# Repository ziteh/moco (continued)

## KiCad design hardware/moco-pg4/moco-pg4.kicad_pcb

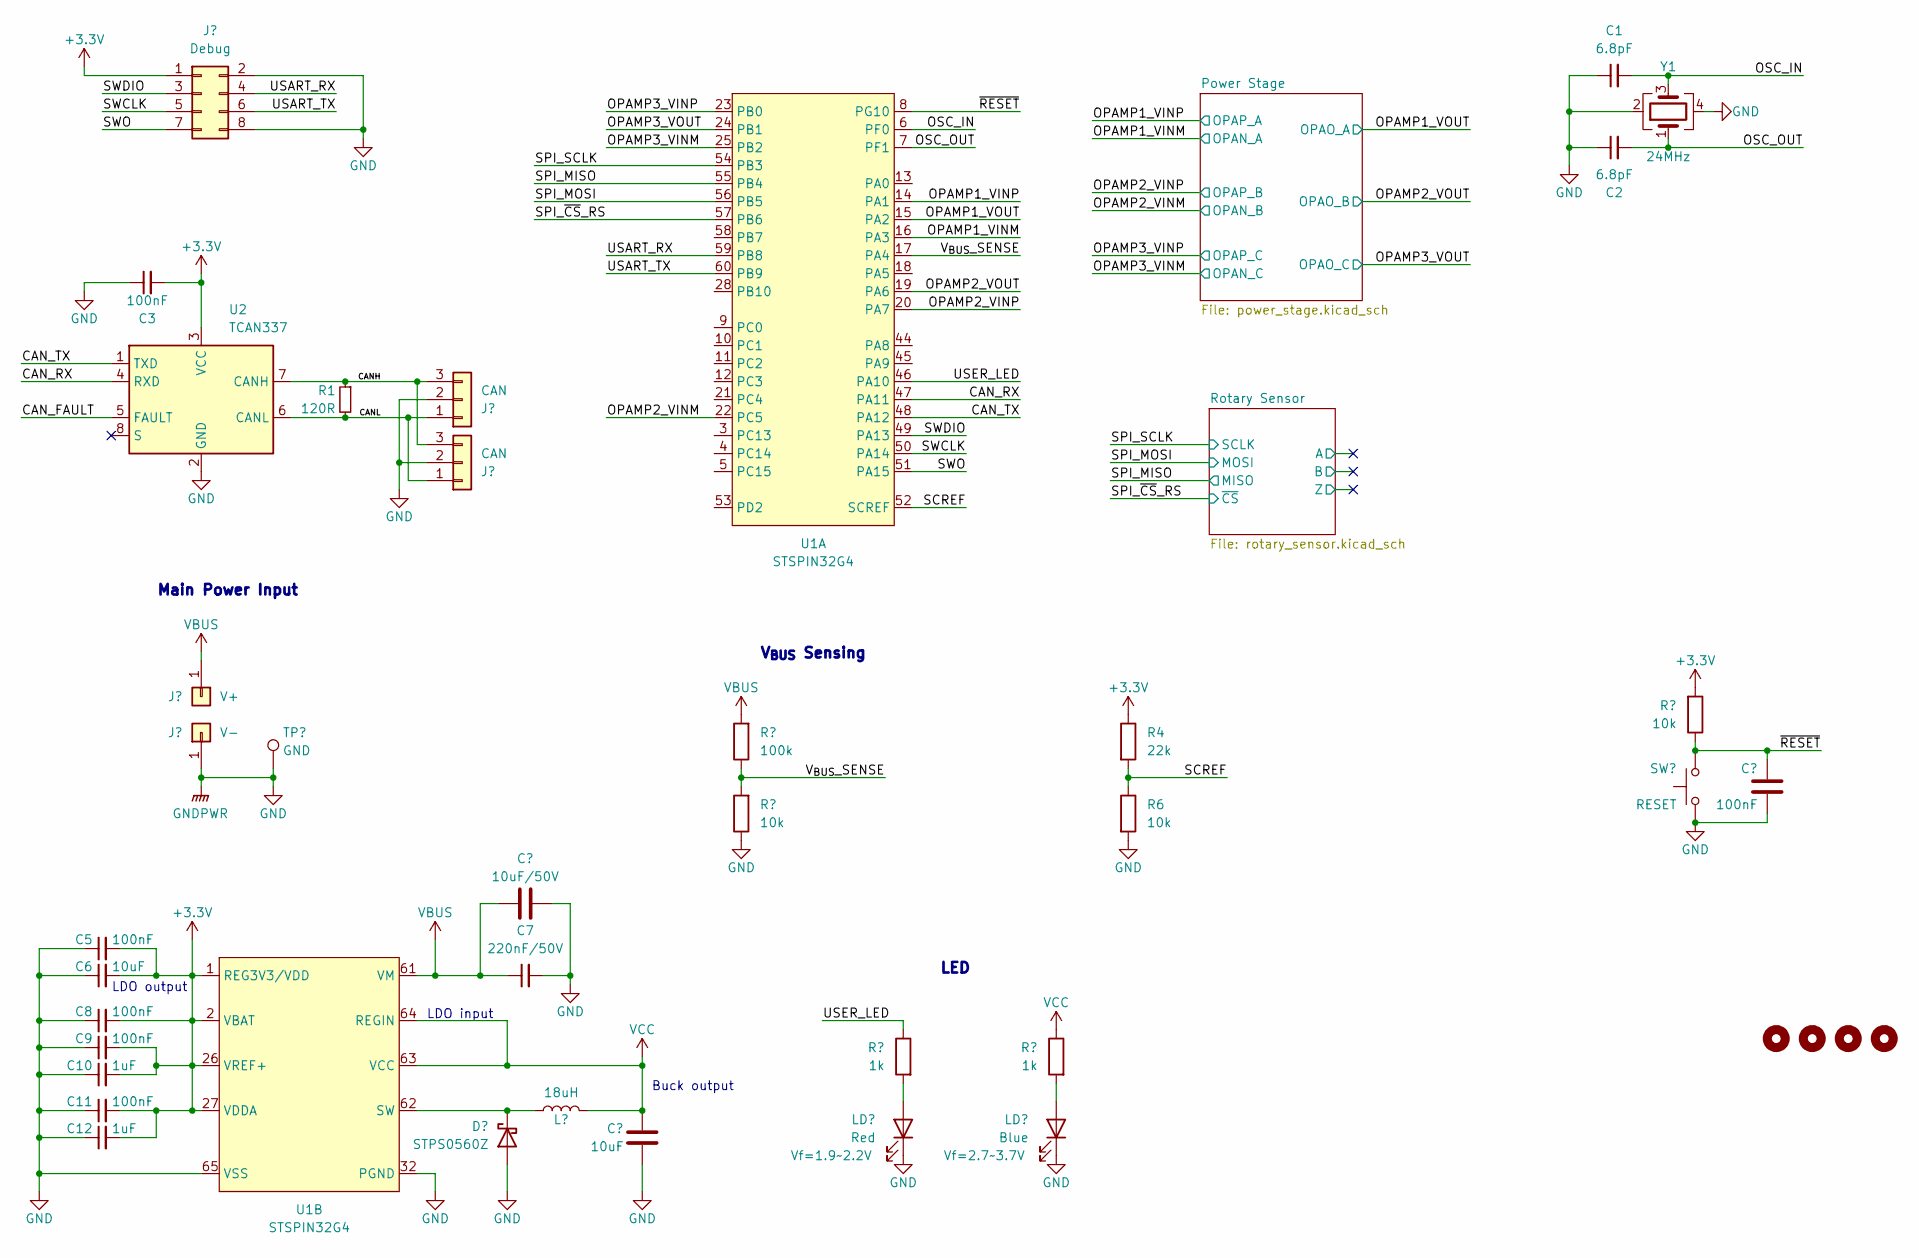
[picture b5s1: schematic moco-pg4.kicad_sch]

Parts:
C1, C2: 6.8pF; C_0402_1005Metric; MFR. Part# 0402CG6R8C500NT; LCSC C1576
C3, C4, C5, C8, C9, C11: 100nF; C_0402_1005Metric; MFR. Part# CL05B104KB54PNC; LCSC C307331
C6: 10uF; C_0402_1005Metric; MFR. Part# CL05A106MQ5NUNC; LCSC C15525
C7: 220nF/50V; C_0805_2012Metric; MFR. Part# CL21B224KBFNNNE; LCSC C5378
C10, C12: 1uF; C_0402_1005Metric; MFR. Part# CL05A105KA5NQNC; LCSC C52923
C13: 10uF; C_0805_2012Metric; MFR. Part# CL21A476MQYNNNE; LCSC C16780
C35: 10uF/50V; C_0805_2012Metric; MFR. Part# GRM21BR61H106KE43L; LCSC C440198
D1: STPS0560Z; D_SOD-123F; MFR. Part# STPS0560Z; LCSC C99285
H1, H2, H3, H4: MountingHole; MountingHole_2.2mm_M2_ISO14580
J1: Debug; PinHeader_2x04_P2.54mm_Vertical
J2, J8: CAN; JST_SH_SM03B-SRSS-TB_1x03-1MP_P1.00mm_Horizontal; MFR. Part# SM03B-SRSS-TB(LF)(SN); LCSC C160403
J3: V+; wire_2.2mm_rectagnel
J4: V-; wire_2.2mm
L1: 18uH; L_Taiyo-Yuden_MD-3030; MFR. Part# YNR3015-220M; LCSC C497564
LD1: Red; LED_0603_1608Metric; MFR. Part# KT-0603R; LCSC C2286
LD2: Blue; LED_0603_1608Metric; MFR. Part# 19-217/GHC-YR1S2/3T; LCSC C72043
R1: 120R; R_0402_1005Metric_Pad0.72x0.64mm_HandSolder; MFR. Part# 0402WGF1200TCE; LCSC C25079
R2, R5, R6: 10k; R_0402_1005Metric; MFR. Part# 0402WGF1002TCE; LCSC C25744
R3: 100k; R_0402_1005Metric; MFR. Part# 0402WGF1003TCE; LCSC C25741
R4: 22k; R_0402_1005Metric; MFR. Part# 0402WGF2202TCE; LCSC C25768
R7, R8: 1k; R_0402_1005Metric; MFR. Part# 0402WGF1001TCE; LCSC C11702
SW1: RESET; SW_SPST_EVQP7C; MFR. Part# 3*4mm
TP1: GND; TestPoint_Pad_D1.0mm
U1: STSPIN32G4; VFQFPN 9X9X1.0 64 PITCH 0.5; MFR. Part# STSPIN32G4; LCSC C2858620
U2: TCAN337; SOT-23-8
Y1: 24MHz; Crystal_SMD_3225-4Pin_3.2x2.5mm; MFR. Part# X322524MSB4SI; LCSC C15643

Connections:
+3.3V: C3.2, C5.2, C6.2, C8.2, C9.2, C10.2, C11.2, C12.2, J1.1, R2.2, R4.1, U1.1 (REG3V3/VDD), U1.2 (VBAT), U1.26 (VREF+), U1.27 (VDDA), U2.3 (VCC); also elsewhere on the board
/CANH: J2.3, J8.3, R1.1, U2.7 (CANH)
/CANL: J2.1, J8.1, R1.2, U2.6 (CANL)
/CAN_FAULT: U2.5 (FAULT)
/CAN_RX: U1.47 (PA11), U2.4 (RXD)
/CAN_TX: U1.48 (PA12), U2.1 (TXD)
/OPAMP1_VINM: U1.16 (PA3); also elsewhere on the board
/OPAMP1_VINP: U1.14 (PA1); also elsewhere on the board
/OPAMP1_VOUT: U1.15 (PA2); also elsewhere on the board
/OPAMP2_VINM: U1.22 (PC5); also elsewhere on the board
/OPAMP2_VINP: U1.20 (PA7); also elsewhere on the board
/OPAMP2_VOUT: U1.19 (PA6); also elsewhere on the board
/OPAMP3_VINM: U1.25 (PB2); also elsewhere on the board
/OPAMP3_VINP: U1.23 (PB0); also elsewhere on the board
/OPAMP3_VOUT: U1.24 (PB1); also elsewhere on the board
/OSC_IN: C1.2, U1.6 (PF0), Y1.3
/OSC_OUT: C2.2, U1.7 (PF1), Y1.1
/SCREF: R4.2, R6.1, U1.52 (SCREF)
/SPI_MISO: U1.55 (PB4); also elsewhere on the board
/SPI_MOSI: U1.56 (PB5); also elsewhere on the board
/SPI_SCLK: U1.54 (PB3); also elsewhere on the board
/SPI_~CS_RS: U1.57 (PB6); also elsewhere on the board
/SWCLK: J1.5, U1.50 (PA14)
/SWDIO: J1.3, U1.49 (PA13)
/SWO: J1.7, U1.51 (PA15)
/USART_RX: J1.4, U1.59 (PB8)
/USART_TX: J1.6, U1.60 (PB9)
/USER_LED: R7.1, U1.46 (PA10)
/V_{BUS}_SENSE: R3.1, R5.2, U1.17 (PA4)
/~RESET: C4.1, R2.1, SW1.1, U1.8 (PG10)
GND: C1.1, C2.1, C3.1, C4.2, C5.1, C6.1, C7.2, C8.1, C9.1, C10.1, C11.1, C12.1, C13.2, D1.2 (A), J1.2, J1.8, J2.2, J4.1, J8.2, LD1.1 (K), LD2.1 (K), R5.1, R6.2, SW1.2, TP1.1, U1.32 (PGND), U1.65 (VSS), U2.2 (GND), Y1.2, Y1.4; also elsewhere on the board
unnamed: D1.1 (K), L1.1, U1.62 (SW)
unnamed: LD1.2 (A), R7.2
unnamed: LD2.2 (A), R8.2
VBUS: C7.1, J3.1, R3.2, U1.61 (VM); also elsewhere on the board
VCC: C13.1, L1.2, R8.1, U1.63 (VCC), U1.64 (REGIN)

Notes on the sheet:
Buck output
LDO output
LED
Main Power Input
V_{BUS} Sensing
LDO input

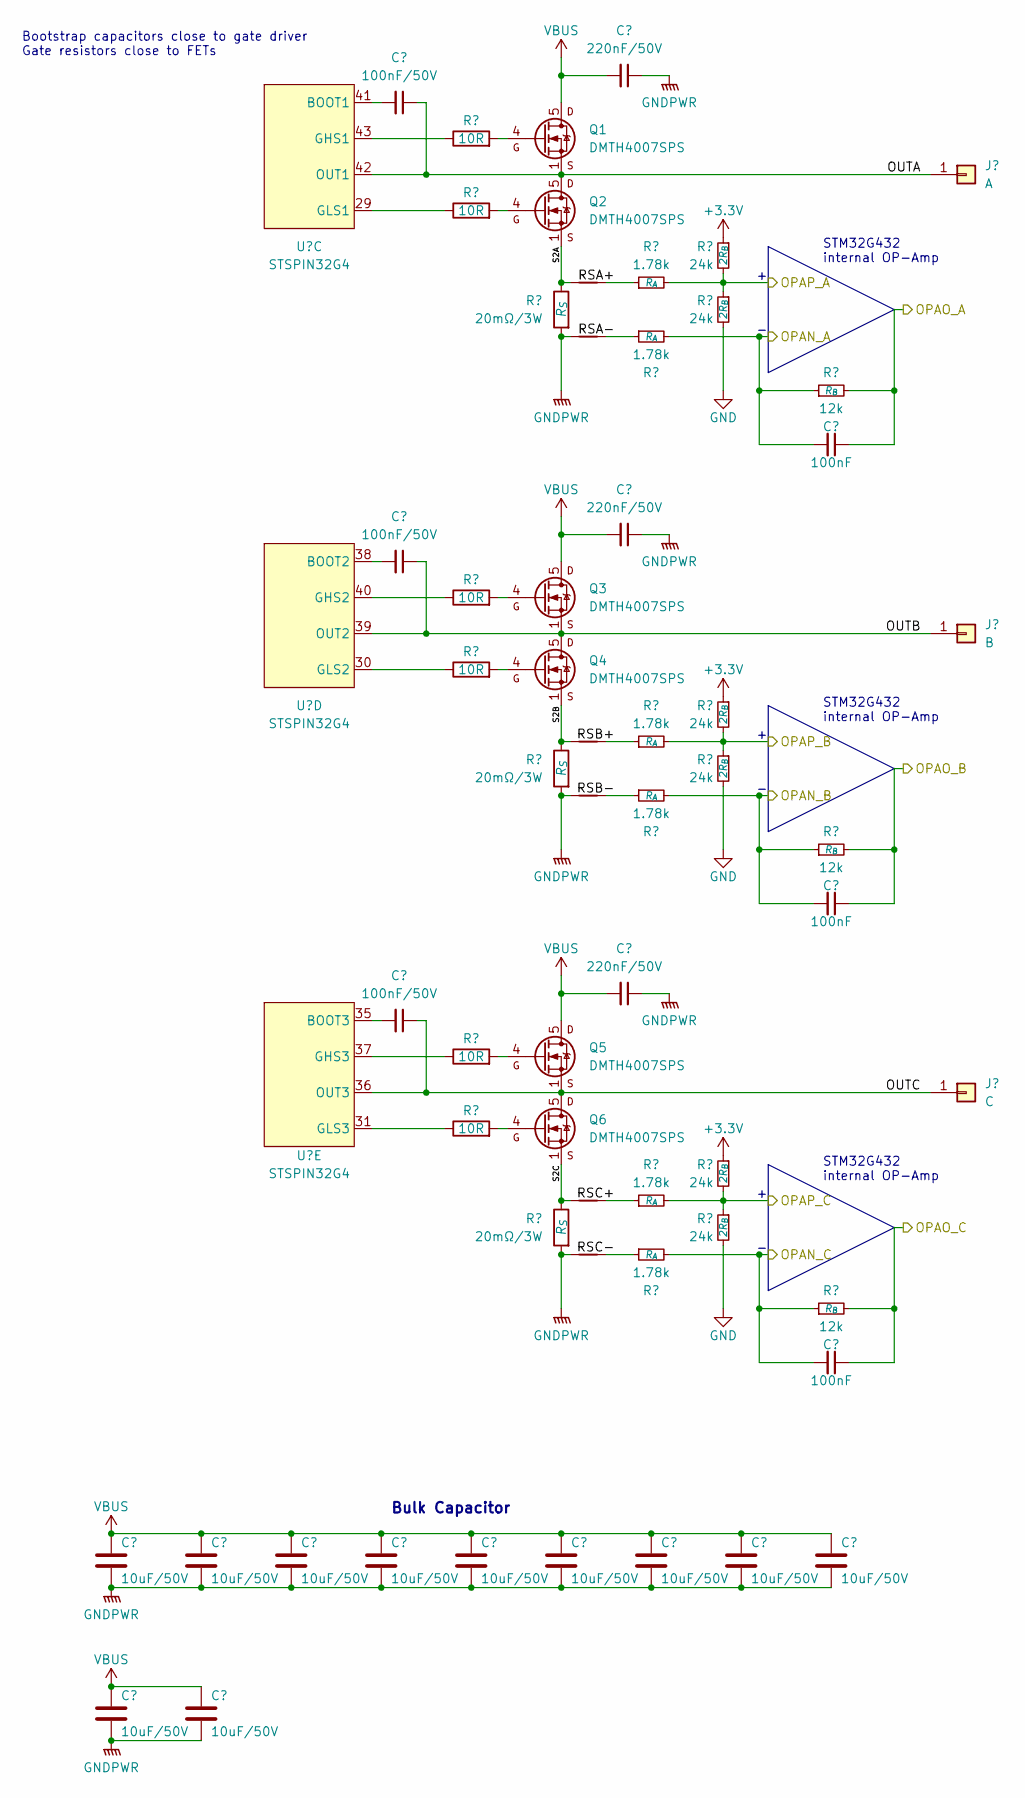
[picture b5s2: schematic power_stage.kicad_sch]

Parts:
C14, C17, C20: 220nF/50V; C_0805_2012Metric; MFR. Part# CL21B224KBFNNNE; LCSC C5378
C15, C18, C21: 100nF/50V; C_0402_1005Metric; MFR. Part# CL05B104KB54PNC; LCSC C307331
C16, C19, C22: 100nF; C_0402_1005Metric; MFR. Part# CL21B224KBFNNNE; LCSC C5378
C23, C24, C25, C26, C27, C28, C29, C30, C31, C33, C34: 10uF/50V; C_0805_2012Metric; MFR. Part# GRM21BR61H106KE43L; LCSC C440198
J5: A; wire_2.2mm_rectagnel
J6: B; wire_2.2mm_rectagnel
J7: C; wire_2.2mm_rectagnel
NT1, NT2, NT3, NT4, NT5, NT6: NetTie_2; NetTie-2_SMD_Pad0.5mm
Q1, Q2, Q3, Q4, Q5, Q6: DMTH4007SPS; PowerDI5060-8
R9, R10, R17, R18, R25, R26: 10R; R_0402_1005Metric; MFR. Part# 0402WGF100JTCE; LCSC C25077
R11, R14, R19, R22, R27, R30: 24k; R_0402_1005Metric; MFR. Part# 0402WGF2402TCE; LCSC C25769
R12, R15, R20, R23, R28, R31: 1.78k; R_0402_1005Metric; MFR. Part# ARG02FTC1781; LCSC C284379
R13, R21, R29: 20mΩ/3W; R_2512_6332Metric; MFR. Part# CRA2512-FZ-R020ELF; LCSC C840620
R16, R24, R32: 12k; R_0402_1005Metric; MFR. Part# 0402WGF1202TCE; LCSC C25752
U1: STSPIN32G4; VFQFPN 9X9X1.0 64 PITCH 0.5; MFR. Part# STSPIN32G4; LCSC C2858620

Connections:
+3.3V: R11.1, R19.1, R27.1; also elsewhere on the board
/OPAMP1_VINM: C16.2, R15.2, R16.1; also elsewhere on the board
/OPAMP1_VINP: R11.2, R12.2, R14.1; also elsewhere on the board
/OPAMP1_VOUT: C16.1, R16.2; also elsewhere on the board
/OPAMP2_VINM: C19.2, R23.2, R24.1; also elsewhere on the board
/OPAMP2_VINP: R19.2, R20.2, R22.1; also elsewhere on the board
/OPAMP2_VOUT: C19.1, R24.2; also elsewhere on the board
/OPAMP3_VINM: C22.2, R31.2, R32.1; also elsewhere on the board
/OPAMP3_VINP: R27.2, R28.2, R30.1; also elsewhere on the board
/OPAMP3_VOUT: C22.1, R32.2; also elsewhere on the board
/Power Stage/OUTA: C15.1, J5.1, Q1.1 (S), Q1.2 (S), Q1.3 (S), Q2.5 (D), Q2.6 (D), Q2.7 (D), Q2.8 (D), U1.42 (OUT1)
/Power Stage/OUTB: C18.1, J6.1, Q3.1 (S), Q3.2 (S), Q3.3 (S), Q4.5 (D), Q4.6 (D), Q4.7 (D), Q4.8 (D), U1.39 (OUT2)
/Power Stage/OUTC: C21.1, J7.1, Q5.1 (S), Q5.2 (S), Q5.3 (S), Q6.5 (D), Q6.6 (D), Q6.7 (D), Q6.8 (D), U1.36 (OUT3)
/Power Stage/RSA+: NT1.1, R12.1
/Power Stage/RSA-: NT2.1, R15.1
/Power Stage/RSB+: NT3.1, R20.1
/Power Stage/RSB-: NT4.1, R23.1
/Power Stage/RSC+: NT5.1, R28.1
/Power Stage/RSC-: NT6.1, R31.1
/Power Stage/S2A: NT1.2, Q2.1 (S), Q2.2 (S), Q2.3 (S), R13.1
/Power Stage/S2B: NT3.2, Q4.1 (S), Q4.2 (S), Q4.3 (S), R21.1
/Power Stage/S2C: NT5.2, Q6.1 (S), Q6.2 (S), Q6.3 (S), R29.1
GND: C14.1, C17.1, C20.1, C23.2, C24.2, C25.2, C26.2, C27.2, C28.2, C29.2, C30.2, C31.2, C33.2, C34.2, NT2.2, NT4.2, NT6.2, R13.2, R14.2, R21.2, R22.2, R29.2, R30.2; also elsewhere on the board
unnamed: Q1.4 (G), R9.2
unnamed: Q2.4 (G), R10.2
unnamed: Q3.4 (G), R17.2
unnamed: Q4.4 (G), R18.2
unnamed: Q5.4 (G), R25.2
unnamed: Q6.4 (G), R26.2
unnamed: C15.2, U1.41 (BOOT1)
unnamed: R9.1, U1.43 (GHS1)
unnamed: R10.1, U1.29 (GLS1)
unnamed: C18.2, U1.38 (BOOT2)
unnamed: R17.1, U1.40 (GHS2)
unnamed: R18.1, U1.30 (GLS2)
unnamed: C21.2, U1.35 (BOOT3)
unnamed: R25.1, U1.37 (GHS3)
unnamed: R26.1, U1.31 (GLS3)
VBUS: C14.2, C17.2, C20.2, C23.1, C24.1, C25.1, C26.1, C27.1, C28.1, C29.1, C30.1, C31.1, C33.1, C34.1, Q1.5 (D), Q1.6 (D), Q1.7 (D), Q1.8 (D), Q3.5 (D), Q3.6 (D), Q3.7 (D), Q3.8 (D), Q5.5 (D), Q5.6 (D), Q5.7 (D), Q5.8 (D); also elsewhere on the board

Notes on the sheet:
Bulk Capacitor
STM32G432 internal OP-Amp
Bootstrap capacitors close to gate driver Gate resistors close to FETs

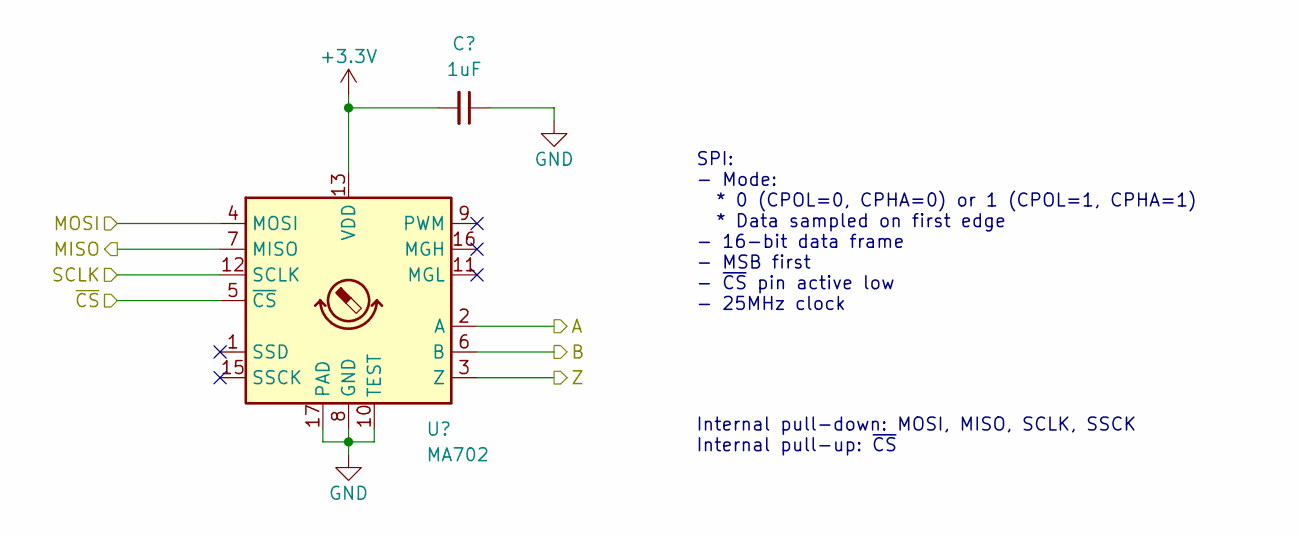
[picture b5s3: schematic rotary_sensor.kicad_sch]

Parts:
C36: 1uF; C_0402_1005Metric_Pad0.74x0.62mm_HandSolder; MFR. Part# CL05A105KA5NQNC; LCSC C52923
U3: MA702; QFN-16-1EP_3x3mm_P0.5mm_EP1.75x1.75mm; MFR. Part# MA702GQ-Z

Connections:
+3.3V: C36.2, U3.13 (VDD); also elsewhere on the board
/Rotary Sensor/A: U3.2 (A)
/Rotary Sensor/B: U3.6 (B)
/Rotary Sensor/Z: U3.3 (Z)
/SPI_MISO: U3.7 (MISO); also elsewhere on the board
/SPI_MOSI: U3.4 (MOSI); also elsewhere on the board
/SPI_SCLK: U3.12 (SCLK); also elsewhere on the board
/SPI_~CS_RS: U3.5 (~CS); also elsewhere on the board
GND: C36.1, U3.8 (GND), U3.10 (TEST), U3.17 (PAD); also elsewhere on the board

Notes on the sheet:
Internal pull-down: MOSI, MISO, SCLK, SSCK Internal pull-up: ~{CS}
SPI: - Mode: * 0 (CPOL=0, CPHA=0) or 1 (CPOL=1, CPHA=1) * Data sampled on first edge - 16-bit data frame - MSB first - ~{CS} pin active low - 25MHz clock

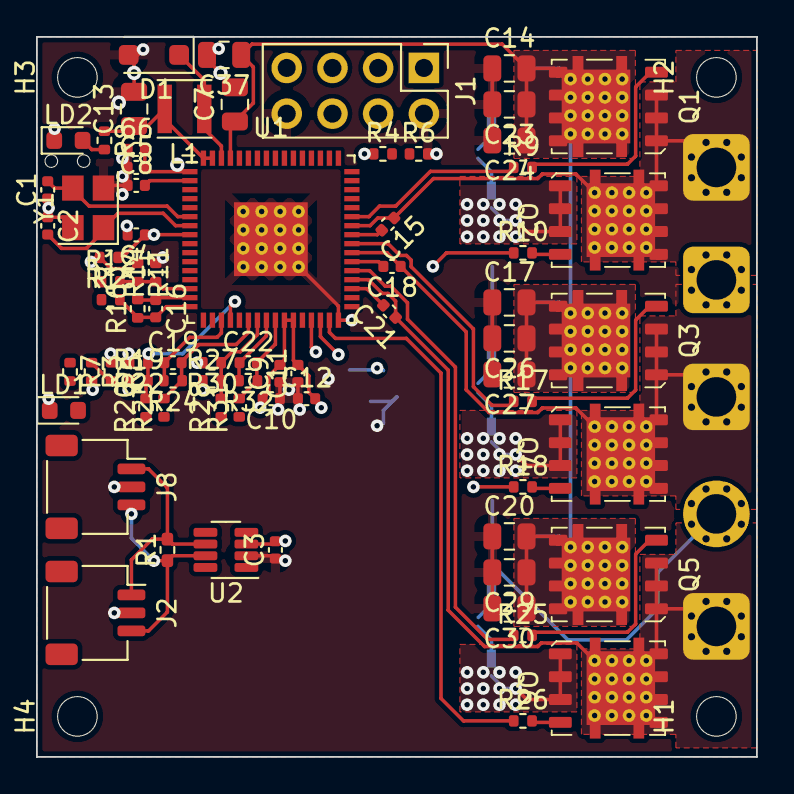
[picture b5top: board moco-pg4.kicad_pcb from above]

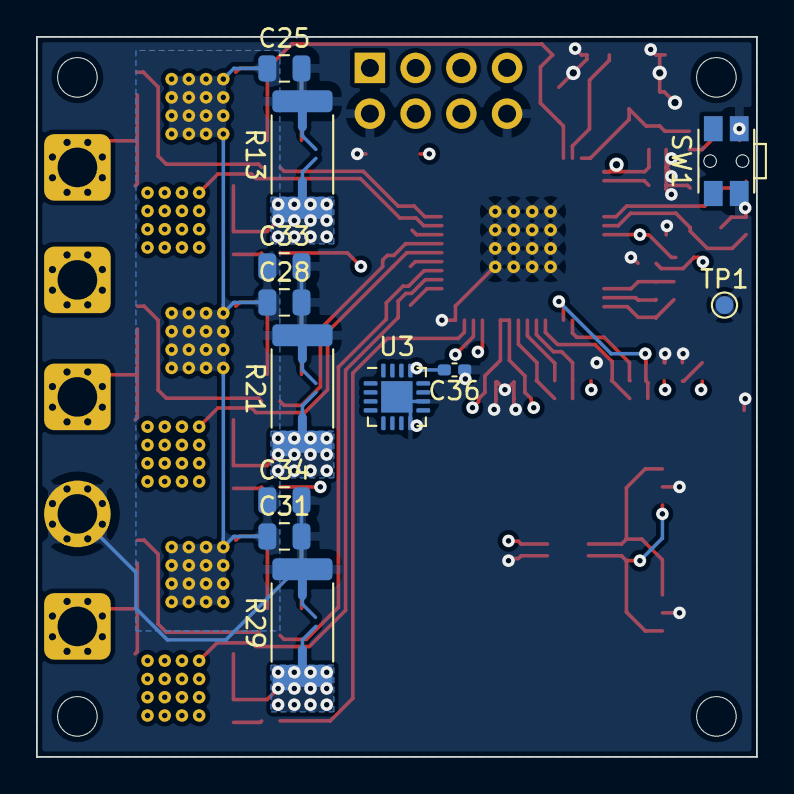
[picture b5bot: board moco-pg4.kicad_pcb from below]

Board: 4 copper layers, 40.0 x 40.0 mm, 101 parts (18 on the bottom side), 62 nets.

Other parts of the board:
C37: 10uF/50V; C_0805_2012Metric

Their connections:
GND: C37.2; also elsewhere on the board
VBUS: C37.1; also elsewhere on the board

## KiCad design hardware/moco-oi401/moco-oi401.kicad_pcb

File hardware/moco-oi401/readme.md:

# moco-OI401

- 10V~35V operating voltage
- 8A peak current
- 3x or 6xPWM control
- 3-Phase low-side current sense
- Ø40mm round PCB
- 3xM2 mounting holes, P.C.D Ø35.5mm
- [STM32G431CBU6](https://www.st.com/en/microcontrollers-microprocessors/stm32g431cb.html) 170 MHz MCU
- [DRV8316C](https://www.ti.com/product/DRV8316C) gate driver integrated FETs
- AS5047x magnetic encoder

## Pinmap

| Description              | DRV8316 | STM32 | STM32 Func |
| ------------------------ | ------- | ----- | ---------- |
| PWM-A High               | INHA    | PA10  | TIM1_CH3   |
| PWM-B High               | INHB    | PA9   | TIM1_CH2   |
| PWM-C High               | INHC    | PA8   | TIM1_CH1   |
| PWM-A Low                | INLA    | PC15  | TIM1_CH3N  |
| PWM-B Low                | INLB    | PA12  | TIM1_CH2N  |
| PWM-C Low                | INLC    | PB13  | TIM1_CH1N  |
| Current sense A          | SOA     | PA5   | ADC2_IN13  |
| Current sense B          | SOB     | PA6   | ADC2_IN3   |
| Current sense C          | SOC     | PA7   | ADC2_IN4   |
| nEnable                  | DRVOFF  | PB12  |            |
| nFAULT                   | nFAULT  | PB11  |            |
| SPI SCLK                 | SCLK    | PB3   | SPI1       |
| SPI MISO                 | SDI     | PB4   | SPI1       |
| SPI MOSI                 | SDO     | PB5   | SPI1       |
| SPI nCS DRV8316          | nSCS    | PB9   |            |
| SPI nCS AS5047x          | --      | PB2   |            |
| USART Tx                 | --      | PA2   | USART2     |
| USART Rx                 | --      | PA3   | USART2     |
| User LED 1 (Red)         | --      | PA0   | Active LOW |
| User LED 2 (Blue)        | --      | PA1   | Active LOW |
| 5V indicator LED (Green) | --      | --    |            |

## Jumper
- SB1 (3.3V LDO Bypass)
  - ON: 3.3V LDO bypassed, 3.3V provided through the buck regulator of DRV8316.
  - OFF (Default): 3.3V provided through the LDO.
- SB2 (nSLEEP Reset)
  - ON: Connected DRV8316 `nSLEEP` pin to RESET button.
  - OFF (Default): Disconnected DRV8316 `nSLEEP` pin to RESET button.
- SB3 (Voltage Reference Selection)
  - ON (Default): Connected +3.3V to STM32 `VREF+` and DRV8316 `VREF/LILM`, `VREF+` used as input.
  - OFF: Disconnected +3.3V to STM32 `VREF+` and DRV8316 `VREF/LILM`, voltage reference powered by STM32G4 embed voltage reference buffer, `VREF+` used as output.

## SPI

- Mode=1
  - CPOL=0. Clock is low when idle.
  - CPHA=1. Data sampled on 2nd edge (i.e. falling edge).
- 16-bit data frame.
- MSB first.
- nCS pin active low.
- 5MHz clock (limited by DRV8316).

## Board Characteristics

- Copper layer count: 2
- Board overall dimensions: 40 x 40 mm
- Min track/spacing: 0.13 mm / 0.13 mm
- Min hole diameter: 0.3 mm
- Castellated pads: No
- Edge card connectors: No
- Plated board edge: No

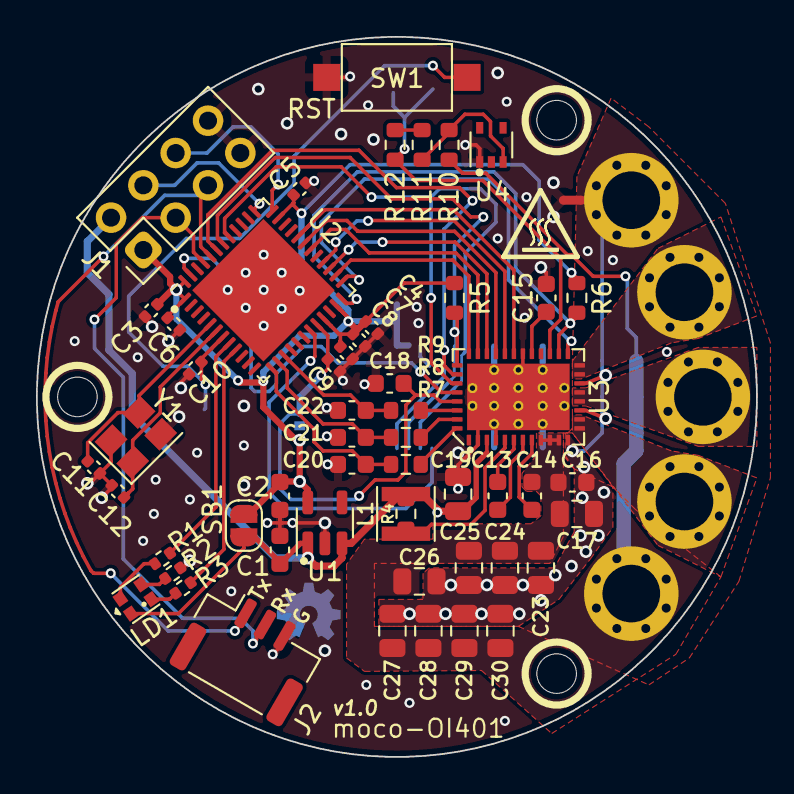
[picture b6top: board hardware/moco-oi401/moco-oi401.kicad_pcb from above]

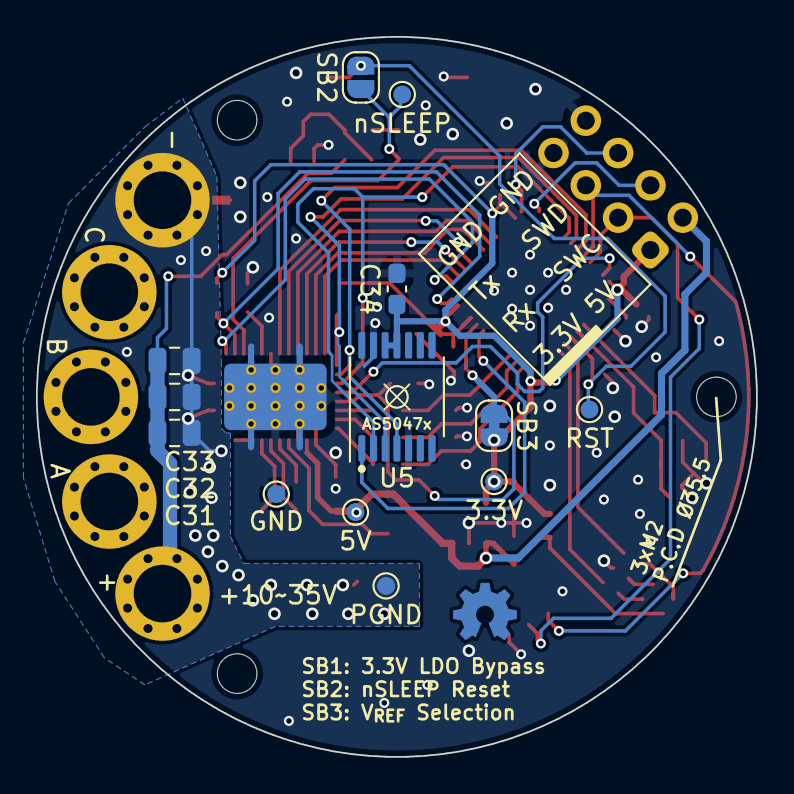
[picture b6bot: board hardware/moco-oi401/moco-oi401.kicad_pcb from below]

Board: 2 copper layers, 40.0 x 40.0 mm, 75 parts (13 on the bottom side), 48 nets.

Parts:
C1, C2: 1uF; C_0603_1608Metric
C3, C4, C5, C6, C9, C10: 100nF; C_0402_1005Metric
C7: 10nF; C_0402_1005Metric
C8: 1uF; C_0402_1005Metric
C11, C12: 12pF; C_0402_1005Metric
C13: 47nF/50V; C_0603_1608Metric
C14: 1uF/16V; C_0603_1608Metric
C15: 1uF/6.3V; C_0603_1608Metric
C16: 100nF/50V; C_0603_1608Metric
C17, C23, C24, C25, C26, C27, C28, C29, C30, C31, C32, C33: 10uF/50V; C_0805_2012Metric
C18: 100nF/6.3V; C_0603_1608Metric
C19: 22uF/16V; C_0805_2012Metric
C20, C21, C22: 22pF; C_0603_1608Metric
C34: 100nF; C_0603_1608Metric_Pad1.08x0.95mm_HandSolder
H1, H2, H3: MountingHole; MountingHole_2.2mm_M2_ISO14580
J1: Debug; PinHeader_2x04_P2.54mm_Vertical
J2: Serial; JST_GH_SM03B-GHS-TB_1x03-1MP_P1.25mm_Horizontal
J3: V+; wire_3.2mm
J4: V-; wire_3.2mm
J5: A; wire_3.2mm
J6: B; wire_3.2mm
J7: C; wire_3.2mm
L1: 47uH; L_Taiyo-Yuden_MD-3030
LD1: LED_BAGR; RGB LED 1.6x1.6mm
NT1: NetTie_2; NetTie-2_SMD_Pad0.5mm
R1, R3: 1k; R_0402_1005Metric
R2: 5.1k; R_0402_1005Metric
R4: 22R; R_0603_1608Metric
R5, R6: 5.1k; R_0603_1608Metric
R7, R8, R9: 330R; R_0603_1608Metric
R10: 10k/100mW; R_0603_1608Metric
R11, R12: 10k; R_0603_1608Metric
SB1, SB2: SolderJumper_2_Open; SolderJumper-2_P1.3mm_Open_RoundedPad1.0x1.5mm
SB3: SolderJumper_2_Bridged; SolderJumper-2_P1.3mm_Bridged_RoundedPad1.0x1.5mm
SW1: RESET; SW_SPST_CK_RS282G05A3
TP1: ~{RESET}; TestPoint_Pad_D1.0mm
TP2: V_{CC}; TestPoint_Pad_D1.0mm
TP3: GND; TestPoint_Pad_D1.0mm
TP4: V_{BK}; TestPoint_Pad_D1.0mm
TP5: PGND; TestPoint_Pad_D1.0mm
TP6: nSLEEP; TestPoint_Pad_D1.0mm
U1: RT9013-33GB; SOT-23-5
U2: STM32G431CBUx; QFN-48-1EP_7x7mm_P0.5mm_EP5.6x5.6mm
U3: DRV8316CR; VQFN-40_RGF_5x7mm_0.5mm_pitch_thermalpad
U4: LM4040A50; SOT-353_SC-70-5
U5: AS5047x; TSSOP-14_4.4x5mm_P0.65mm
Y1: 16MHz; Crystal_SMD_3225-4Pin_3.2x2.5mm

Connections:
+3.3V: C2.1, C3.1, C4.1, C5.1, C6.1, C7.1, C8.1, C34.2, J1.1, R5.1, R6.1, SB1.2 (B), SB3.2 (B), TP2.1, U1.5 (VOUT), U2.1 (VBAT), U2.21 (VDDA), U2.23 (VDD), U2.35 (VDD), U2.48 (VDD), U5.11 (VDD), U5.12 (VDD3V3)
+5V: C1.1, C19.2, J1.2, L1.2, LD1.2 (A), R4.2, SB1.1 (A), TP4.1, U1.1 (VIN), U1.3 (EN), U3.3 (FB_BK)
/ Rotary Sensor/MISO: R5.2, U2.42 (PB4), U3.33 (SDO), U5.3 (MISO)
/ Rotary Sensor/MOSI: U2.43 (PB5), U3.34 (SDI), U5.4 (MOSI)
/ Rotary Sensor/SCLK: U2.41 (PB3), U3.35 (SCLK), U5.2 (CLK)
/ Rotary Sensor/~CS: U2.19 (PB2), U5.1 (~CS)
/Driver/AVDD: C15.2, U3.25 (AVDD)
/Driver/DRVOFF: U2.25 (PB12), U3.21 (DRVOFF)
/Driver/INHA: U2.32 (PA10), U3.27 (INHA)
/Driver/INHB: U2.31 (PA9), U3.29 (INHB)
/Driver/INHC: U2.30 (PA8), U3.31 (INHC)
/Driver/INLA: U2.28 (PB15), U3.28 (INLA)
/Driver/INLB: U2.27 (PB14), U3.30 (INLB)
/Driver/INLC: U2.26 (PB13), U3.32 (INLC)
/Driver/OUTA: J5.1, U3.13 (OUTA), U3.14 (OUTA)
/Driver/OUTB: J6.1, U3.16 (OUTB), U3.17 (OUTB)
/Driver/OUTC: J7.1, U3.19 (OUTC), U3.20 (OUTC)
/Driver/SOA: C20.1, R7.1, U2.13 (PA5)
/Driver/SOB: C21.1, R8.1, U2.14 (PA6)
/Driver/SOC: C22.1, R9.1, U2.15 (PA7)
/Driver/V_{REF}: C9.1, C18.1, SB3.1 (A), U2.20 (VREF+), U3.37 (VREF/LILM)
/Driver/~CS: U2.47 (PB9), U3.36 (nSCS)
/Driver/~FAULT: R6.2, U2.24 (PB11), U3.22 (nFAULT)
/Driver/~SLEEP: R12.2, SB2.1 (A), TP6.1, U3.23 (nSLEEP)
/MCU/OSC_IN: C11.2, U2.5 (PF0), Y1.3
/MCU/OSC_OUT: C12.2, U2.6 (PF1), Y1.1
/SWCLK: J1.4, U2.37 (PA14)
/SWDIO: J1.6, U2.36 (PA13)
/UART1_RX: J1.3, J2.2, U2.45 (PB7)
/UART1_TX: J1.5, J2.1, U2.44 (PB6)
/USER_LED1: R1.2, U2.8 (PA0)
/USER_LED2: R3.2, U2.9 (PA1)
/~RESET: C10.1, SB2.2 (B), SW1.2, TP1.1, U2.7 (PG10)
GND: C1.2, C2.2, C3.2, C4.2, C5.2, C6.2, C7.2, C8.2, C9.2, C10.2, C11.1, C12.1, C15.1, C18.2, C19.1, C20.2, C21.2, C22.2, C34.1, J1.7, J1.8, J2.3, NT1.2, R2.2, SW1.1, TP3.1, U1.2 (GND), U2.49 (VSS), U3.2 (AGND), U3.4 (GND_BK), U3.26 (AGND), U3.41 (EP), U4.1 (A), U5.5 (TST), U5.13 (GND), Y1.2, Y1.4
GNDPWR: C16.1, C17.1, C23.2, C24.2, C25.2, C26.2, C27.2, C28.2, C29.2, C30.2, C31.2, C32.2, C33.2, J4.1, NT1.1, TP5.1, U3.12 (PGND), U3.15 (PGND), U3.18 (PGND)
unnamed: LD1.1 (BK), R3.1
unnamed: LD1.3 (GK), R2.1
unnamed: LD1.4 (RK), R1.1
unnamed: R11.2, R12.1
unnamed: C14.1, U3.8 (CP)
unnamed: C13.2, U3.7 (CPH)
unnamed: C13.1, U3.6 (CPL)
unnamed: R7.2, U3.40 (SOA)
unnamed: R8.2, U3.39 (SOB)
unnamed: R9.2, U3.38 (SOC)
unnamed: L1.1, R4.1, U3.5 (SW_BK)
unnamed: R10.2, R11.1, U4.3 (K)
Vdrive: C14.2, C16.2, C17.2, C23.1, C24.1, C25.1, C26.1, C27.1, C28.1, C29.1, C30.1, C31.1, C32.1, C33.1, J3.1, R10.1, U3.9 (VM), U3.10 (VM), U3.11 (VM)

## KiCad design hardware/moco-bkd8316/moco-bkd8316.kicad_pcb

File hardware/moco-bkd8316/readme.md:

# moco-bkd8316

- [DRV8316](https://www.ti.com/product/DRV8316) 40V max 8A peak, gate driver + FETs power stage + current sensing.

## PCB

### Board Characteristics

- Copper layer count: 2
- Board overall dimensions: 35.5 x 41 mm
- Min track/spacing: 0.2 mm / 0.2 mm
- Min hole diameter: 0.3 mm
- Castellated pads: No
- Edge card connectors: No
- Plated board edge: No

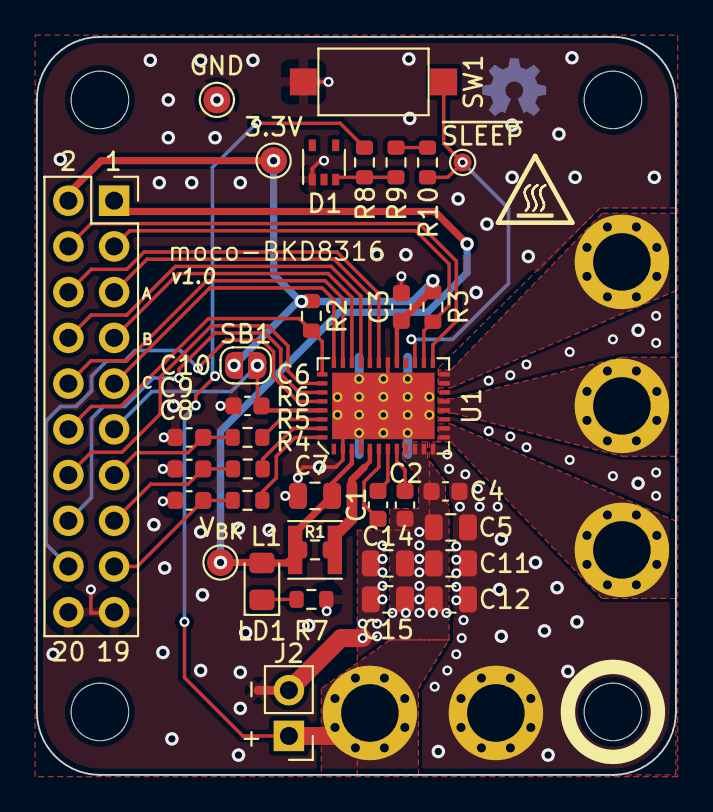
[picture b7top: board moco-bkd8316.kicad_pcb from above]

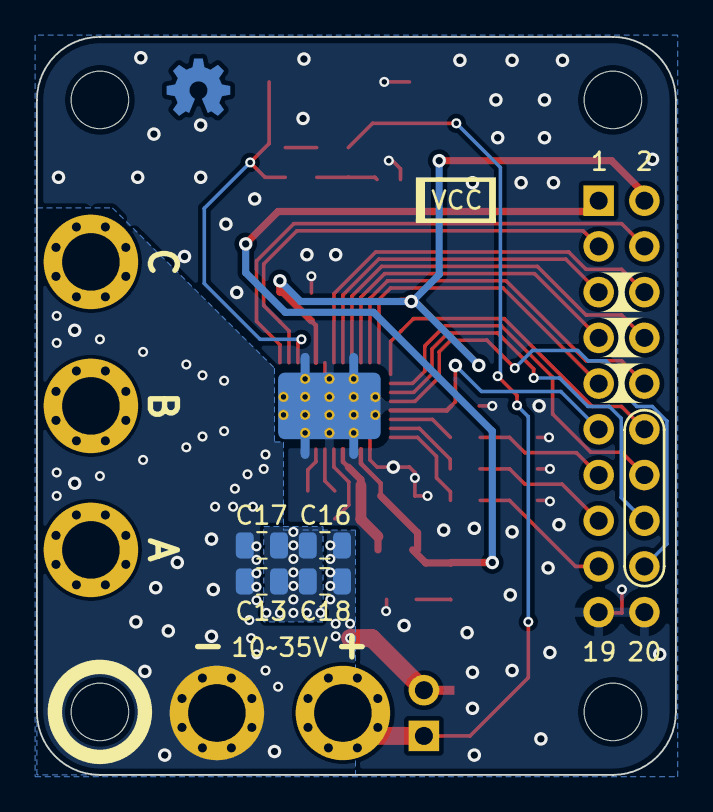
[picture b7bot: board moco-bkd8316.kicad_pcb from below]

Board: 2 copper layers, 35.5 x 41.0 mm, 50 parts (4 on the bottom side), 35 nets.

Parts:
C1: 47nF/50V; C_0603_1608Metric
C2: 1uF/16V; C_0603_1608Metric
C3: 1uF/6.3V; C_0603_1608Metric
C4: 100nF/50V; C_0603_1608Metric
C5, C11, C12, C13, C14, C15, C16, C17, C18: 10uF/50V; C_0805_2012Metric
C6: 100nF/6.3V; C_0603_1608Metric
C7: 22uF/16V; C_0805_2012Metric
C8, C9, C10: 22pF; C_0603_1608Metric
D1: LM4040A50; SOT-353_SC-70-5
H1, H2, H3, H4: MountingHole; MountingHole_3.2mm_M3
J1: Conn_02x10_Odd_Even; PinSocket_2x10_P2.54mm_Vertical
J2: Conn_01x02; PinHeader_1x02_P2.54mm_Vertical
J3, J4, J5: A; wire_3.2mm
J6: B; wire_3.2mm
J7: C; wire_3.2mm
L1: 47uH; L_Taiyo-Yuden_MD-3030
LD1: LED; LED_0805_2012Metric_Pad1.15x1.40mm_HandSolder
NT1: NetTie_2; NetTie-2_SMD_Pad0.5mm
R1: 22R; R_0603_1608Metric
R2, R3: 5.1k; R_0603_1608Metric
R4, R5, R6: 330R; R_0603_1608Metric
R7: 1.5k; R_0603_1608Metric
R8: 10k/100mW; R_0603_1608Metric
R9, R10: 10k; R_0603_1608Metric
SB1: SolderJumper_2_Open; SolderJumper-2_P1.3mm_Open_RoundedPad1.0x1.5mm
SW1: RESET; SW_SPST_CK_RS282G05A3
TP1, TP2, TP3: TestPoint; TestPoint_Pad_D1.5mm
TP4: nSLEEP; TestPoint_Pad_D1.0mm
U1: DRV8316CR; VQFN-40_RGF_5x7mm_0.5mm_pitch_thermalpad

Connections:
+3.3V: C3.2, J1.2, R2.1, R3.1, SB1.2 (B), TP1.1, U1.25 (AVDD)
/OUTA: J5.1, U1.13 (OUTA), U1.14 (OUTA)
/OUTB: J6.1, U1.16 (OUTB), U1.17 (OUTB)
/OUTC: J7.1, U1.19 (OUTC), U1.20 (OUTC)
DRVOFF: J1.4, U1.21 (DRVOFF)
GND: C3.1, C6.2, C7.1, C8.2, C9.2, C10.2, D1.1 (A), J1.19, J1.20, NT1.1, R7.2, SW1.1, TP3.1, U1.2 (AGND), U1.4 (GND_BK), U1.26 (AGND), U1.41 (EP)
GNDPWR: C4.1, C5.1, C11.2, C12.2, C13.2, C14.2, C15.2, C16.2, C17.2, C18.2, J2.2, J4.1, NT1.2, U1.12 (PGND), U1.15 (PGND), U1.18 (PGND)
MISO: J1.12, R2.2, U1.33 (SDO)
MOSI: J1.14, U1.34 (SDI)
unnamed: D1.3 (K), R8.2, R9.1
unnamed: LD1.1 (K), R7.1
unnamed: R9.2, R10.1
unnamed: C2.1, U1.8 (CP)
unnamed: C1.2, U1.7 (CPH)
unnamed: C1.1, U1.6 (CPL)
unnamed: R4.2, U1.40 (SOA)
unnamed: R5.2, U1.39 (SOB)
unnamed: R6.2, U1.38 (SOC)
unnamed: L1.1, R1.1, U1.5 (SW_BK)
PWM_H_A: J1.6, U1.27 (INHA)
PWM_H_B: J1.8, U1.29 (INHB)
PWM_H_C: J1.10, U1.31 (INHC)
PWM_L_A: J1.5, U1.28 (INLA)
PWM_L_B: J1.7, U1.30 (INLB)
PWM_L_C: J1.9, U1.32 (INLC)
SCLK: J1.16, U1.35 (SCLK)
SOA: C8.1, J1.17, R4.1
SOB: C9.1, J1.15, R5.1
SOC: C10.1, J1.13, R6.1
VBUS: C2.2, C4.2, C5.2, C11.1, C12.1, C13.1, C14.1, C15.1, C16.1, C17.1, C18.1, J2.1, J3.1, R8.1, U1.9 (VM), U1.10 (VM), U1.11 (VM)
VCC: C7.2, J1.1, L1.2, LD1.2 (A), R1.2, TP2.1, U1.3 (FB_BK)
VREF: C6.1, J1.11, SB1.1 (A), U1.37 (VREF/LILM)
~CS: J1.18, U1.36 (nSCS)
~FAULT: J1.3, R3.2, U1.22 (nFAULT)
~SLEEP: R10.2, SW1.2, TP4.1, U1.23 (nSLEEP)

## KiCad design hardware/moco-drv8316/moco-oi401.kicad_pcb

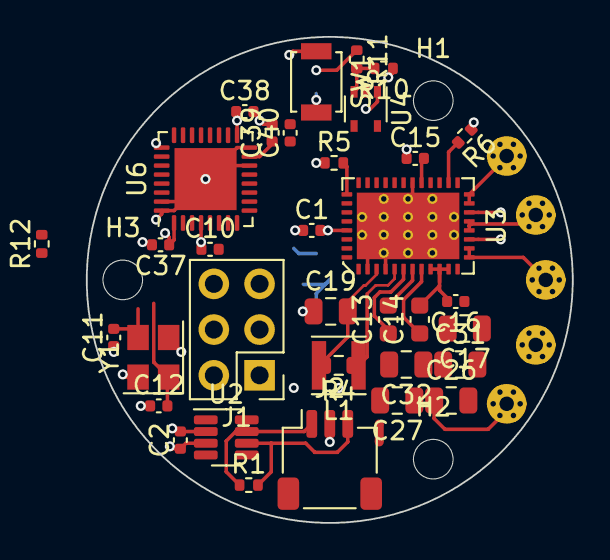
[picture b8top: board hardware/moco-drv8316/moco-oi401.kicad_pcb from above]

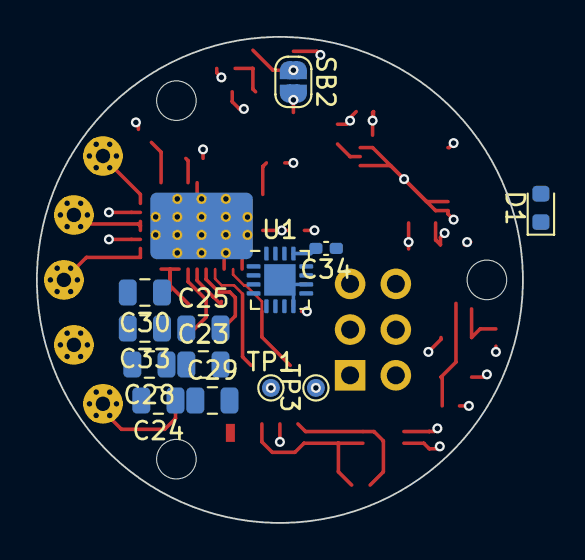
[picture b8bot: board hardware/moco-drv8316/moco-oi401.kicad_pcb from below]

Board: 2 copper layers, 27.0 x 27.0 mm, 57 parts (13 on the bottom side), 40 nets.

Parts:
C1: 100nF/6.3V; C_0402_1005Metric
C2, C40: 1uF; C_0402_1005Metric
C10, C37, C38: 100nF; C_0402_1005Metric
C11, C12: 12pF; C_0402_1005Metric
C13: 47nF/50V; C_0603_1608Metric
C14: 1uF/16V; C_0603_1608Metric
C15: 1uF/6.3V; C_0402_1005Metric
C16: 100nF/50V; C_0402_1005Metric
C17, C23, C24, C25, C26, C27, C28, C29, C30, C31, C32, C33: 10uF/50V; C_0805_2012Metric
C19: 22uF/16V; C_0805_2012Metric
C34: 1uF; C_0402_1005Metric_Pad0.74x0.62mm_HandSolder
C39: 10nF; C_0402_1005Metric
D1: LED; LED_0603_1608Metric
H1, H2, H3: MountingHole; MountingHole_2.2mm_M2_ISO14580
J1: Debug; PinHeader_2x03_P2.54mm_Vertical
J2: Conn_01x03; JST_SH_SM03B-SRSS-TB_1x03-1MP_P1.00mm_Horizontal
J3: V+; wire_0.8mm
J4: V-; wire_0.8mm
J5: A; wire_0.8mm
J6: B; wire_0.8mm
J7: C; wire_0.8mm
L1: 47uH; L_Taiyo-Yuden_MD-3030
NT1: NetTie_2; NetTie-2_SMD_Pad0.5mm
R1: 120R; R_0402_1005Metric
R4: 22R; R_0603_1608Metric
R5, R6: 10k; R_0402_1005Metric
R10, R11: 33k/30mW; R_0402_1005Metric
R12: 1k; R_0402_1005Metric
SB2: SolderJumper_2_Open; SolderJumper-2_P1.3mm_Open_RoundedPad1.0x1.5mm
SW1: RESET; SW_SPST_B3U-1000P
TP1: 3.3V; TestPoint_Pad_D1.0mm
TP3: GND; TestPoint_Pad_D1.0mm
U1: MA730; QFN-16-1EP_3x3mm_P0.5mm_EP1.75x1.75mm
U2: TCAN332; SOT-23-8
U3: DRV8316CR; VQFN-40_RGF_5x7mm_0.5mm_pitch_thermalpad
U4: LM4040A50; SOT-353_SC-70-5
U6: STM32G431KBUx; QFN-32-1EP_5x5mm_P0.5mm_EP3.45x3.45mm
Y1: 16MHz; Crystal_SMD_3225-4Pin_3.2x2.5mm

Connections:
+3.3V: C2.1, C19.2, C34.2, C37.1, C38.1, J1.1, L1.2, R4.2, TP1.1, U1.13 (VDD), U2.3 (VCC), U3.3 (FB_BK), U6.1 (VDD), U6.17 (VDD)
/ Rotary Sensor/MISO: R5.2, U1.7 (MISO), U3.33 (SDO), U6.27 (PB4)
/ Rotary Sensor/MOSI: U1.4 (MOSI), U3.34 (SDI), U6.28 (PB5)
/ Rotary Sensor/SCLK: U1.12 (SCLK), U3.35 (SCLK), U6.26 (PB3)
/ Rotary Sensor/~CS: U1.5 (~CS), U6.9 (PA4)
/CANH: J2.1, R1.1, U2.7 (CANH)
/CANL: J2.3, R1.2, U2.6 (CANL)
/CAN_RX: U2.4 (RXD), U6.21 (PA11)
/CAN_TX: U2.1 (TXD), U6.22 (PA12)
/Driver/DRVOFF: U3.21 (DRVOFF), U6.30 (PB7)
/Driver/INHA: U3.27 (INHA), U6.20 (PA10)
/Driver/INHB: U3.29 (INHB), U6.19 (PA9)
/Driver/INHC: U3.31 (INHC), U6.18 (PA8)
/Driver/OUTA: J5.1, U3.13 (OUTA), U3.14 (OUTA)
/Driver/OUTB: J6.1, U3.16 (OUTB), U3.17 (OUTB)
/Driver/OUTC: J7.1, U3.19 (OUTC), U3.20 (OUTC)
/Driver/SOA: U3.40 (SOA), U6.10 (PA5)
/Driver/SOB: U3.39 (SOB), U6.11 (PA6)
/Driver/SOC: U3.38 (SOC), U6.12 (PA7)
/Driver/~CS: U3.36 (nSCS), U6.29 (PB6)
/Driver/~FAULT: R6.2, U3.22 (nFAULT), U6.25 (PA15)
/Driver/~SLEEP: R11.1, SB2.1 (A), U3.23 (nSLEEP)
/MCU/OSC_IN: C11.2, U6.2 (PF0), Y1.3
/MCU/OSC_OUT: C12.2, U6.3 (PF1), Y1.1
/MCU/USER_LED: D1.2 (A), U6.6 (PA1)
/SWCLK: J1.4, U6.24 (PA14)
/SWDIO: J1.3, U6.23 (PA13)
/UART2_RX: J1.5, U6.8 (PA3)
/UART2_TX: J1.6, U6.7 (PA2)
/~RESET: C10.1, SB2.2 (B), SW1.2, U6.4 (PG10)
GND: C1.1, C2.2, C10.2, C11.1, C12.1, C15.1, C19.1, C34.1, C37.2, C38.2, C39.2, C40.2, J1.2, J2.2, NT1.2, R12.2, SW1.1, TP3.1, U1.8 (GND), U1.10 (TEST), U1.17 (PAD), U2.2 (GND), U3.2 (AGND), U3.4 (GND_BK), U3.26 (AGND), U3.41 (EP), U4.1 (A), U6.14 (VSSA), U6.16 (VSS), U6.31 (PB8), U6.32 (VSS), U6.33 (VSS), Y1.2, Y1.4
GNDPWR: C16.1, C17.1, C23.2, C24.2, C25.2, C26.2, C27.2, C28.2, C29.2, C30.2, C31.2, C32.2, C33.2, J4.1, NT1.1, U3.12 (PGND), U3.15 (PGND), U3.18 (PGND)
unnamed: D1.1 (K), R12.1
unnamed: C14.1, U3.8 (CP)
unnamed: C13.2, U3.7 (CPH)
unnamed: C13.1, U3.6 (CPL)
unnamed: L1.1, R4.1, U3.5 (SW_BK)
unnamed: R10.2, R11.2, U4.3 (K)
VDDA: C1.2, C15.2, C39.1, C40.1, R5.1, R6.1, U3.25 (AVDD), U3.37 (VREF/LILM), U6.15 (VDDA)
Vdrive: C14.2, C16.2, C17.2, C23.1, C24.1, C25.1, C26.1, C27.1, C28.1, C29.1, C30.1, C31.1, C32.1, C33.1, J3.1, R10.1, U3.9 (VM), U3.10 (VM), U3.11 (VM)

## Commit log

2022-11-28 Init commit
2022-12-01 Move files
2022-12-01 Rename KiCad project to `moco-o`
2022-12-02 Add MoCo-S KiCad project
2022-12-02 Update net classes
2022-12-03 Update layout
2022-12-04 Comp MoCo-S
2022-12-04 Update sch
2022-12-04 Update ref
2022-12-06 Use kelvin connection for shunt resistance
2022-12-06 Replace some extended parts to basic parts
2022-12-06 Add PCBA files
2022-12-07 Update doc info
2022-12-07 Create LICENSE
2022-12-16 Update C47, C48 to the correct part number
2023-01-06 Update LED-G resistor value
2023-07-08 Add moco8316 project
2023-07-08 Move KiCad files to hardware/
2023-07-08 Add SimpleFOC firmware example
2023-07-20 Change to DRV8323H
2023-07-20 Update edge
2023-07-20 Rename "moco-o" to "moco-od501"
2023-07-20 Rename "moco8316" to "moco-bkd8316"
2023-07-20 Rename "moco-s" to "moco-rd501"
2023-07-20 Add OI451 KiCad project
2023-07-21 OI451 routed
2023-07-21 Reroute and reduce size to Ø40mm
2023-07-22 Optimize routing
2023-07-22 Rename "OI451" to "OI401"
2023-07-22 Add readme.md fot OI401
2023-07-22 Add OI401 link
2023-07-22 Add pcb info
2023-07-22 Add high temperature warning silkscreen
2023-07-22 Update part#
2023-07-25 BKD8316 routed
2023-07-25 RD401 basic routed
2023-07-25 Routed
2023-07-25 Remove unused CAN bus schematic
2023-07-25 Rename power stage to triple half bridge
2023-07-25 Rename RD401 to RD321
2023-07-28 Add STSPIN32G4 project
2023-07-29 Add drv8316 mini project
2023-07-29 Routed moco-SC1 rev1
2023-07-30 Update parts
2023-07-30 Remove unused files (moco-pg4_2)
2023-07-30 Change to 4 layers board
2023-07-30 Update connector
2023-07-30 Update board characteristics
2023-07-30 Remove unused files
2023-07-30 Add .lck to gitignore
2023-08-08 Add SimpleFOC firmware for moco-BKD8316
2023-08-08 Add simpleFOC firmware for moco-SC1
2023-08-08 Fix the bug of params
2024-01-14 Update license
2024-03-02 Create TMC4671 KiCad project
2024-03-03 Update schematic
2024-03-23 Remove old firmware of moco-sc1
2024-03-23 Add new firmware of moco-sc1
2024-03-26 Add moco-rc1 KiCad Project
2024-03-30 Fix SVPWM (fabs())
2024-03-30 Add SC2
2024-03-30 Add kicad lib submodule
2024-03-30 Update SC2
2024-03-30 Add SP1
2024-04-09 Update sp1 pcb
2024-05-15 Add redame
2024-05-15 Update REAMDE
2024-05-18 Modify MX config, enable TIM1_CH4 TRGO as current sensing ADC trigger, and enable current sending ADC
2024-05-18 Add ADC injection conversion
2024-05-18 Refactor
2024-05-18 Add spell check config
